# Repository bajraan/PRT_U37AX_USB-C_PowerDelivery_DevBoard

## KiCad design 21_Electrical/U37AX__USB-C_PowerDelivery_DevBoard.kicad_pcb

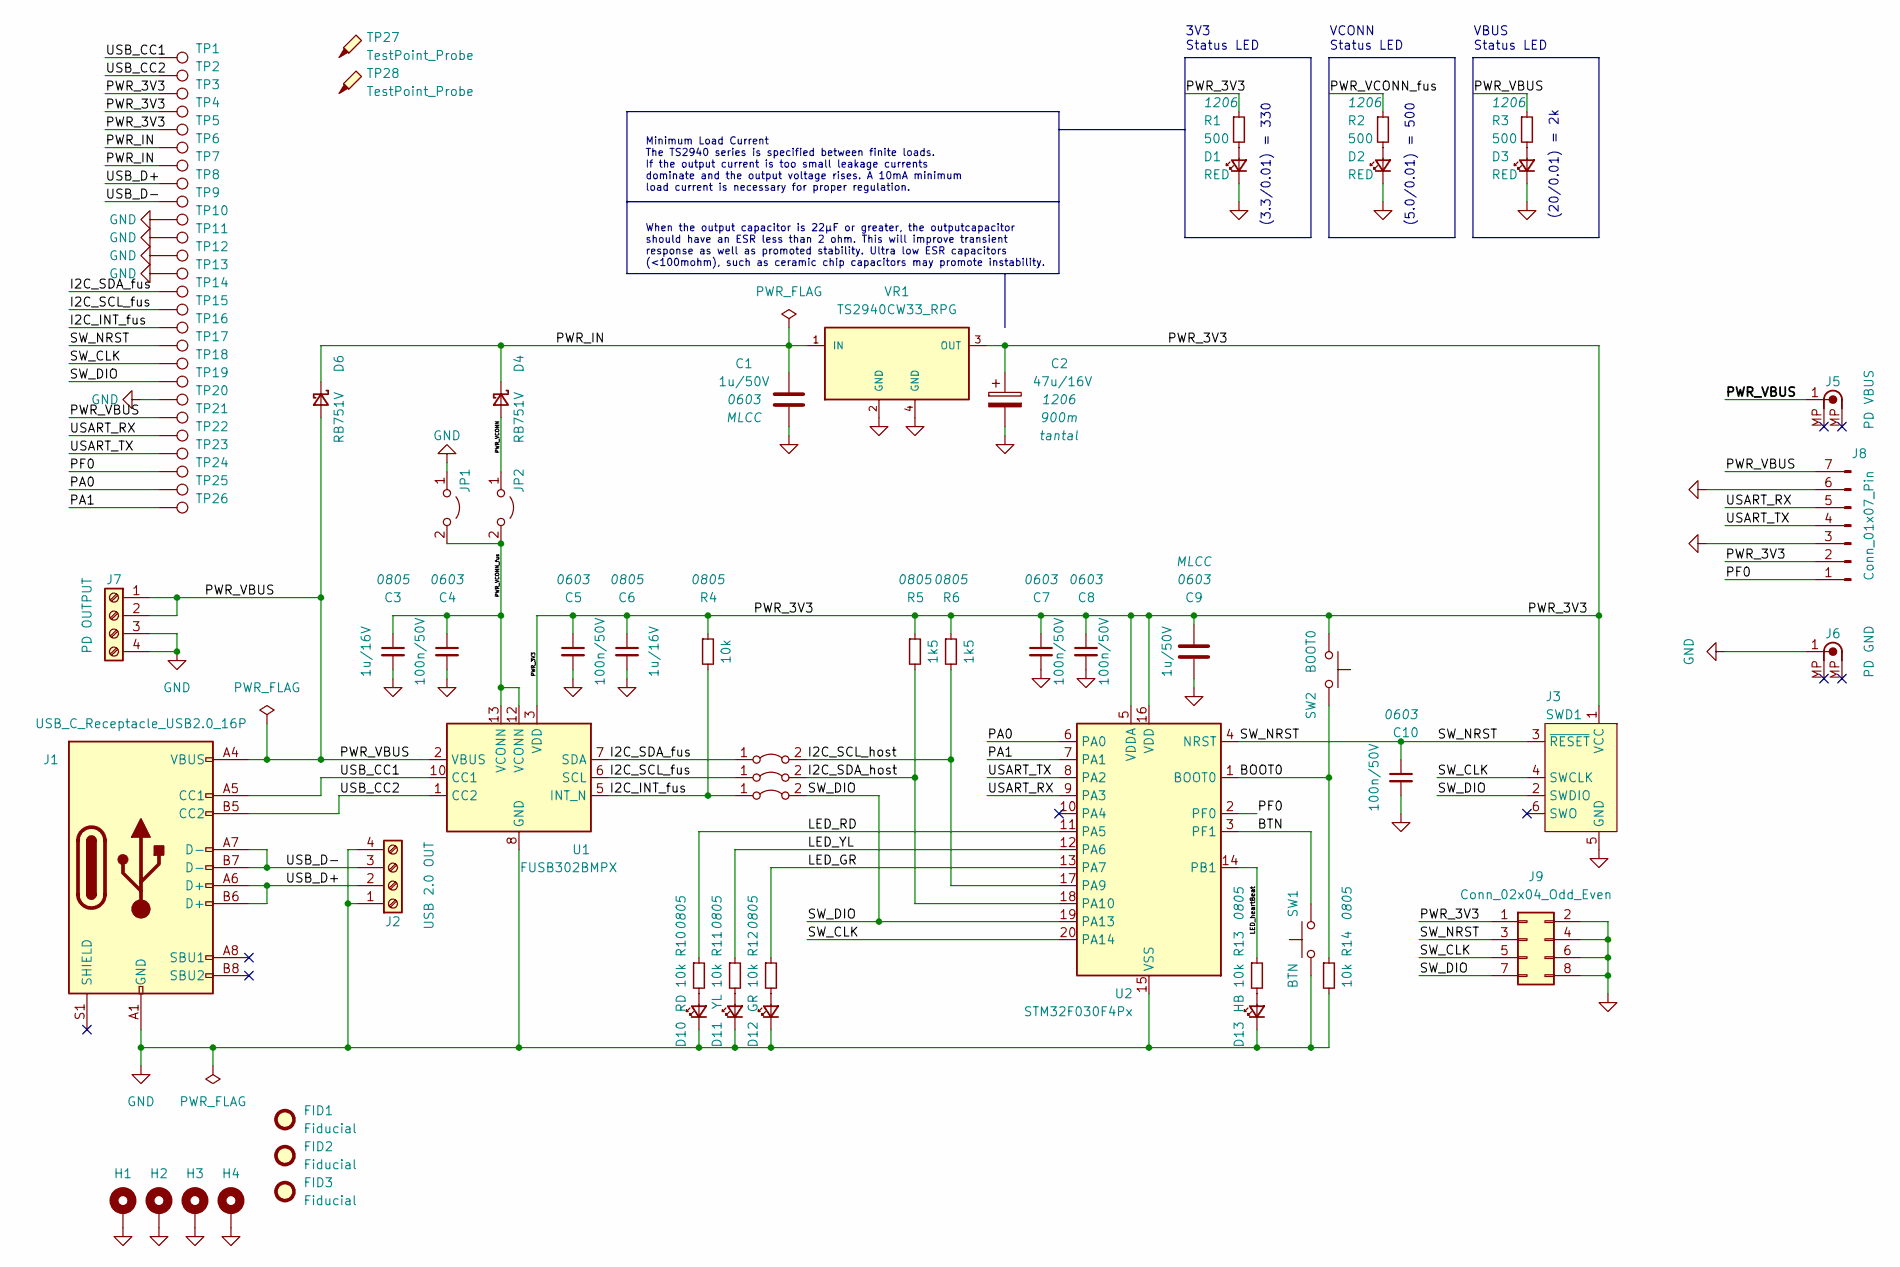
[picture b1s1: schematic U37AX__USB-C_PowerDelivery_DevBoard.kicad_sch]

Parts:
C1, C9: 1u/50V; C_0603_1608Metric_Pad1.08x0.95mm_HandSolder
C2: 47u/16V; CP_EIA-6032-28_Kemet-C_Pad2.25x2.35mm_HandSolder
C3, C6: 1u/16V; C_0805_2012Metric_Pad1.18x1.45mm_HandSolder
C4, C5, C7, C8, C10: 100n/50V; C_0603_1608Metric_Pad1.08x0.95mm_HandSolder
D1, D2, D3: RED; LED_1206_3216Metric_Pad1.42x1.75mm_HandSolder
D4, D6: RB751V; D_SOD-323F
D10: RD; LED_1206_3216Metric_Pad1.42x1.75mm_HandSolder
D11: YL; LED_1206_3216Metric_Pad1.42x1.75mm_HandSolder
D12: GR; LED_1206_3216Metric_Pad1.42x1.75mm_HandSolder
D13: HB; LED_1206_3216Metric_Pad1.42x1.75mm_HandSolder
FID1, FID2, FID3: Fiducial; Fiducial_0.5mm_Mask1.5mm
H1, H2, H3, H4: MountingHole_Pad; MountingHole_3.2mm_M3_Pad_Via
J1: USB_C_Receptacle_USB2.0_16P; GCT_USB4520-03-0-A_REVA
J2: USB 2.0 OUT; RHDR4W100P0X500_1X4_2140X820X1210P
J3: SWD1; Tag-Connect_TC2030-IDC-NL_2x03_P1.27mm_Vertical
J5: PD VBUS; SWEB 8094 RED
J6: PD GND; SWEB 8094 BLACK
J7: PD OUTPUT; RHDR4W100P0X500_1X4_2140X820X1210P
J8: Conn_01x07_Pin; PinSocket_1x07_P2.54mm_Vertical
J9: Conn_02x04_Odd_Even; PinSocket_2x04_P2.54mm_Vertical
JP1, JP2, JP3, JP4, JP5: Jumper_2_Open; TestPoint_2Pads_Pitch2.54mm_Drill0.8mm
R1, R2, R3: 500; R_1206_3216Metric_Pad1.30x1.75mm_HandSolder
R4, R10, R11, R12, R13, R14: 10k; R_0805_2012Metric_Pad1.20x1.40mm_HandSolder
R5, R6: 1k5; R_0805_2012Metric_Pad1.20x1.40mm_HandSolder
SW1: BTN; SW_SPST_TL3305A
SW2: BOOT0; SW_SPST_TL3305A
TP1, TP2, TP3, TP4, TP5, TP6, TP7, TP8, TP9, TP10, TP11, TP12, TP13, TP14, TP15, TP16, TP17, TP18, TP19, TP20, TP21, TP22, TP23, TP24, TP25, TP26: TestPoint; TestPoint_Pad_D1.0mm
TP27, TP28: TestPoint_Probe; TestPoint_Keystone_5019_Minature
U1: FUSB302BMPX; MLP14_2P5X2P5_ONS
U2: STM32F030F4Px; TSSOP-20_4.4x6.5mm_P0.65mm
VR1: TS2940CW33_RPG; PARTREV E15

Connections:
/BOOT0: R14.1, SW2.2, U2.1 (BOOT0)
/BTN: SW1.2, U2.3 (PF1)
/I2C_INT_fus: JP5.1 (A), R4.2, TP16.1, U1.5 (INT_N)
/I2C_SCL_fus: JP4.1 (A), TP15.1, U1.6 (SCL)
/I2C_SCL_host: JP3.2 (B), R6.2, U2.17 (PA9)
/I2C_SDA_fus: JP3.1 (A), TP14.1, U1.7 (SDA)
/I2C_SDA_host: JP4.2 (B), R5.2, U2.18 (PA10)
/LED_GR: R12.1, U2.13 (PA7)
/LED_RD: R10.1, U2.11 (PA5)
/LED_YL: R11.1, U2.12 (PA6)
/LED_heartBeat: R13.1, U2.14 (PB1)
/PA0: TP25.1, U2.6 (PA0)
/PA1: TP26.1, U2.7 (PA1)
/PF0: J8.1, TP24.1, U2.2 (PF0)
/PWR_3V3: C2.1, C5.1, C6.1, C7.1, C8.1, C9.1, J3.1 (VCC), J8.2, J9.1, R1.1, R4.1, R5.1, R6.1, SW2.1, TP3.1, TP4.1, TP5.1, U1.3 (VDD), U1.4 (VDD), U2.5 (VDDA), U2.16 (VDD), VR1.3 (OUT)
/PWR_IN: C1.1, D4.1 (K), D6.1 (K), TP6.1, TP7.1, VR1.1 (IN)
/PWR_VBUS: D6.2 (A), J1.A4 (VBUS), J1.A9 (VBUS), J1.B4 (VBUS), J1.B9 (VBUS), J5.1, J7.1, J7.2, J8.7, R3.1, TP21.1, U1.2 (VBUS)
/PWR_VCONN: D4.2 (A), JP2.1 (A)
/PWR_VCONN_fus: C3.1, C4.1, JP1.2 (B), JP2.2 (B), R2.1, U1.12 (VCONN), U1.13 (VCONN)
/SW_CLK: J3.4 (SWCLK), J9.5, TP18.1, U2.20 (PA14)
/SW_DIO: J3.2 (SWDIO), J9.7, JP5.2 (B), TP19.1, U2.19 (PA13)
/SW_NRST: C10.1, J3.3 (~RESET), J9.3, TP17.1, U2.4 (NRST)
/USART_RX: J8.5, TP22.1, U2.9 (PA3)
/USART_TX: J8.4, TP23.1, U2.8 (PA2)
/USB_CC1: J1.A5 (CC1), TP1.1, U1.10 (CC1), U1.11 (CC1)
/USB_CC2: J1.B5 (CC2), TP2.1, U1.1 (CC2), U1.14 (CC2)
/USB_D+: J1.A6 (D+), J1.B6 (D+), J2.2, TP8.1
/USB_D-: J1.A7 (D-), J1.B7 (D-), J2.3, TP9.1
GND: C1.2, C2.2, C3.2, C4.2, C5.2, C6.2, C7.2, C8.2, C9.2, C10.2, D1.1 (K), D2.1 (K), D3.1 (K), D10.1 (K), D11.1 (K), D12.1 (K), D13.1 (K), H1.1, H2.1, H3.1, H4.1, J1.A1 (GND), J1.A12 (GND), J1.B1 (GND), J1.B12 (GND), J2.1, J2.4, J3.5 (GND), J6.1, J7.3, J7.4, J8.3, J8.6, J9.2, J9.4, J9.6, J9.8, JP1.1 (A), R14.2, SW1.1, TP10.1, TP11.1, TP12.1, TP13.1, TP20.1, U1.8 (GND), U1.9 (GND), U1.15 (GND), U2.15 (VSS), VR1.2 (GND), VR1.4 (GND)
unnamed: D1.2 (A), R1.2
unnamed: D2.2 (A), R2.2
unnamed: D3.2 (A), R3.2
unnamed: D10.2 (A), R10.2
unnamed: D11.2 (A), R11.2
unnamed: D12.2 (A), R12.2
unnamed: D13.2 (A), R13.2

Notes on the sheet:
(5.0/0.01) = 500
VBUS Status LED
VCONN Status LED
Minimum Load Current The TS2940 series is specified between finite loads. If the output current is too small leakage currents dominate and the output voltage rises. A 10mA minimum load current is necessary for proper regulation.
When the output capacitor is 22µF or greater, the outputcapacitor should have an ESR less than 2 ohm. This will improve transient response as well as promoted stability. Ultra low ESR capacitors (<100mohm), such as ceramic chip capacitors may promote instability.
(20/0.01) = 2k
3V3 Status LED
(3.3/0.01) = 330

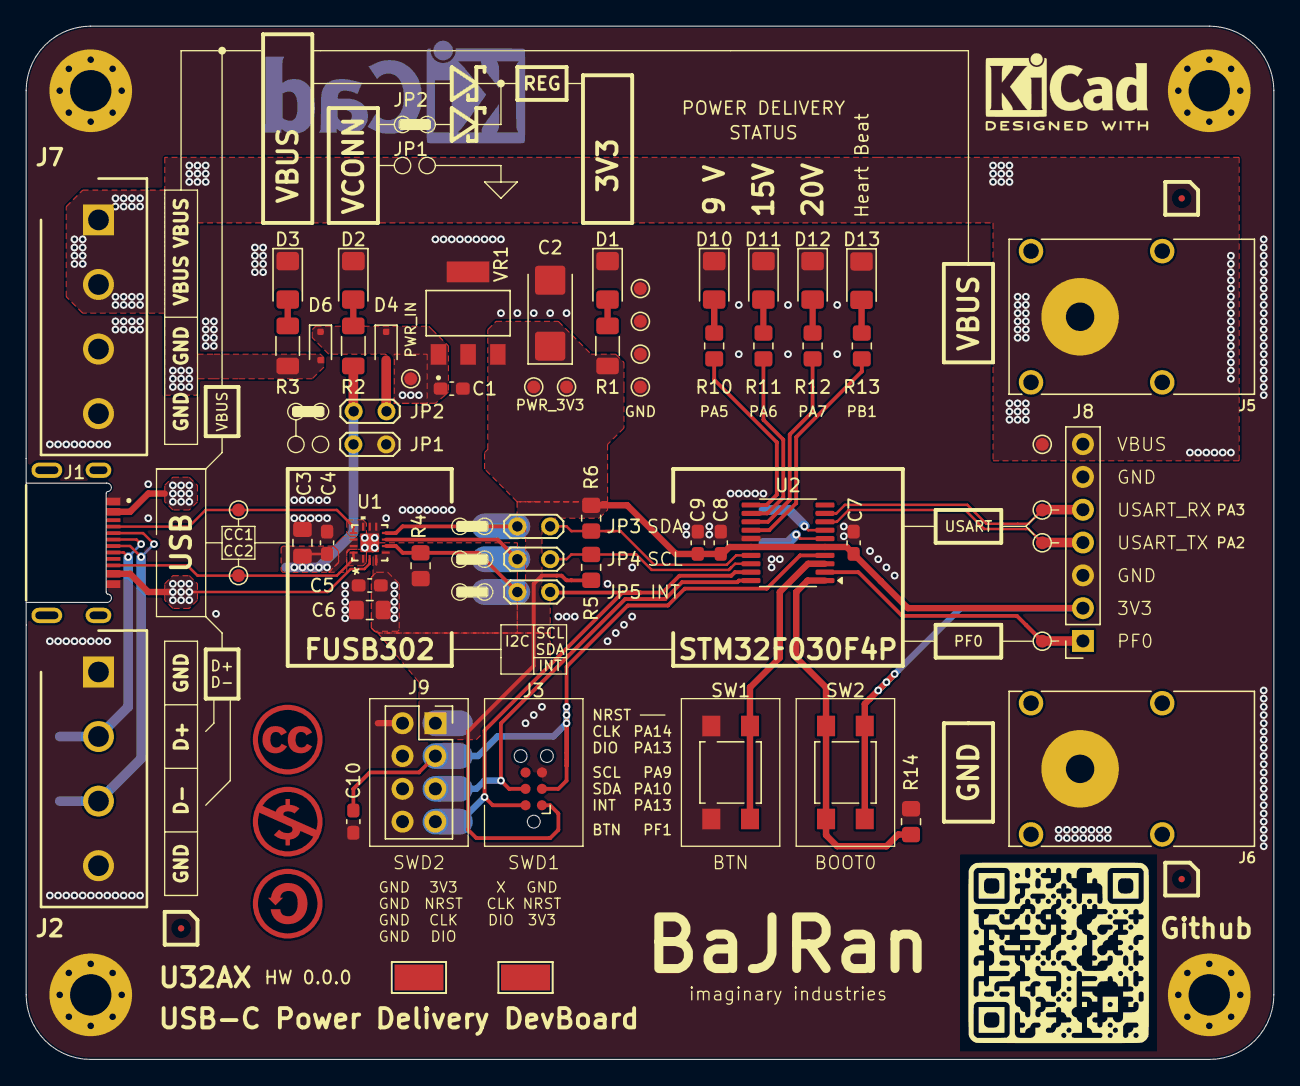
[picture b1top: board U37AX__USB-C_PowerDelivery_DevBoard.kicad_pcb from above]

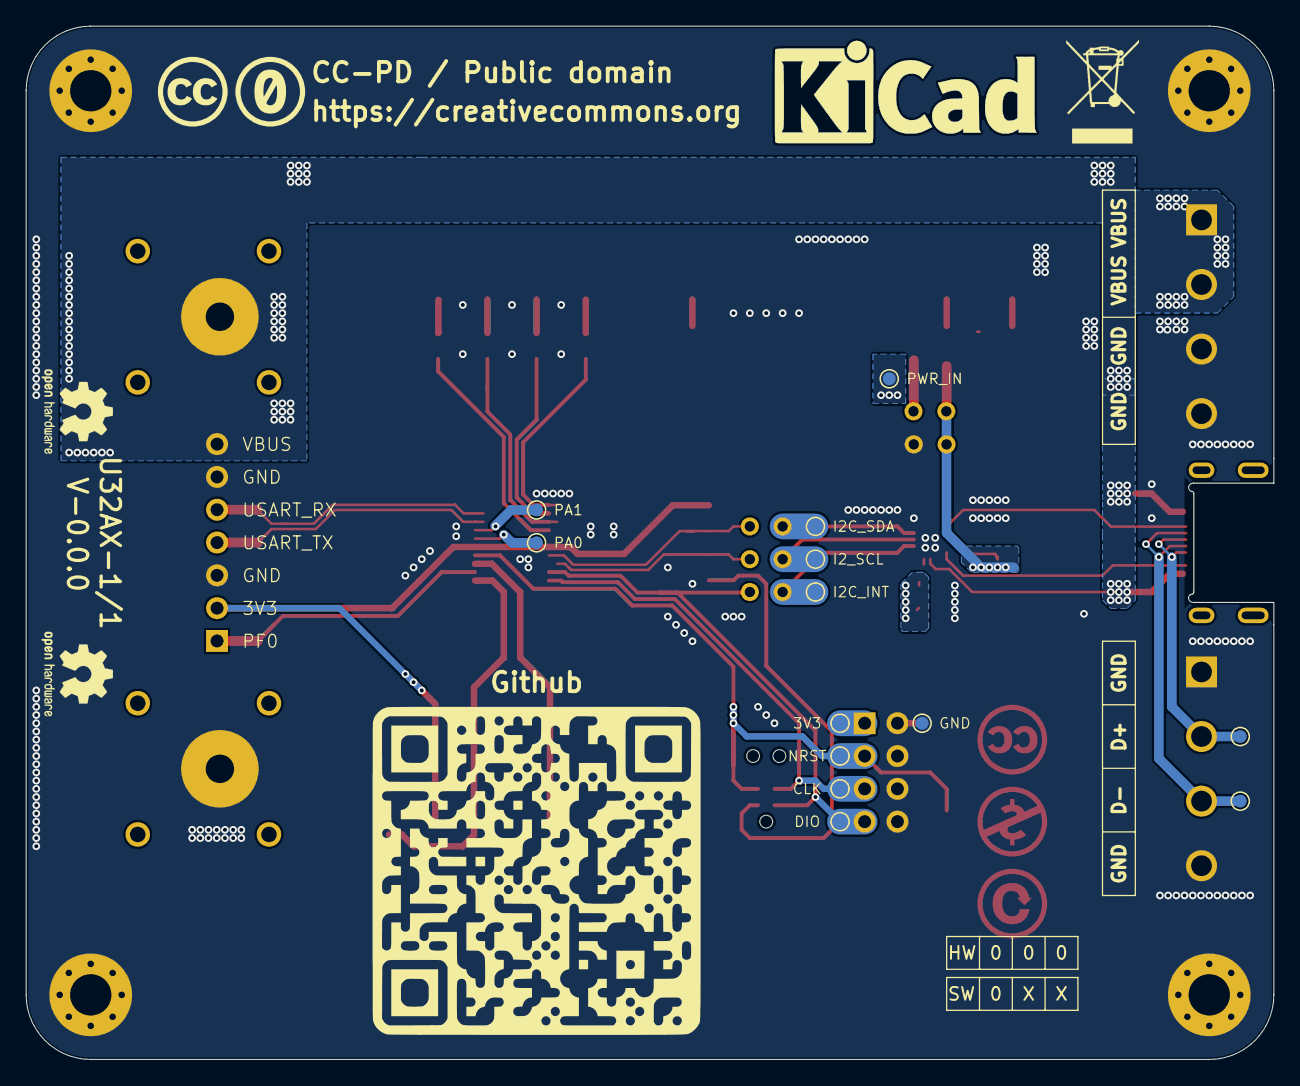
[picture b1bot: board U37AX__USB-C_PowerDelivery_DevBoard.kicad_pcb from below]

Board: 2 copper layers, 96.6 x 80.0 mm, 89 parts (14 on the bottom side), 36 nets.

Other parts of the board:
Github: LOGO; URL_QrCode_0.55x0.55in
Github#2: LOGO; URL_QrCode_1.00x1.00in
Symbol1: Symbol_CreativeCommons_CopperTop_Type2_Small
Symbol2: Symbol_CC-Noncommercial_CopperTop_Small
Symbol3: Symbol_CC-ShareAlike_CopperTop_Small
kicad1: KiCad-Logo2_5mm_SilkScreen

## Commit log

2024-06-25 Qr_Code creation, Qr_Code footprint creation, adding Qr_Code to the PCB project
2024-06-25 .gitignore update
2024-06-25 deleting backup files
2024-06-25 removing .svg
2024-06-25 deleting autosave file
2024-06-25 flayer update
2024-06-26 added TODO.txt for pcb

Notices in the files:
parts and their libraries:
CC-PD / Public domain
